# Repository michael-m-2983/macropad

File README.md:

# macropad

A custom macropad designed by me.

## BOM

| Qty | Item            | Source | Details                                                |
| --- | --------------- | ------ | ------------------------------------------------------ |
| 1   | Case            |        | The case is two seperate parts. It will be 3D printed. |
| 1   | PCB             |        | Designed using KiCad.                                  |
| 1   | Microcontroller | Kit    | Using the Seeed XIAO RP2040                            |
| 1   | OLED Display    | Kit    | 0.91"                                                  |
| 5   | Switch          | Kit    | "MX-style"                                             |
| 5   | Keycaps         | Kit    | Blank white DSA keycaps                                |
| 1   | Rotary Encoder  | Kit    | EC11, Alps                                             |
| 4   | Screws          | Kit    | M3x16mm                                                |

## Components

### Case

The case was designed using [onshape](https://onshape.com/).

It is seperated into two pieces: 

#### Case Top

The top piece has holes for the buttons, OLED screen, rotary encoder, and the screws to attach it to the bottom part.

#### Case Bottom

The bottom part of the case is composed of a baseplate and four walls that are on top of it. The four corners of the walls have holes for screws meant to attach the top part of the case. The wall nearest to the MCU has a hole for the USB-C connector so that it can be accessed easily.

### PCB

The PCB was designed with [KiCad](https://www.kicad.org/), an open-source electronics design software. 

The design of the PCB started with a schematic that dictates which components must be connected to each other:

After this schematic was completed, the traces on the PCB had to be drawn. Here is what the final result looks like:

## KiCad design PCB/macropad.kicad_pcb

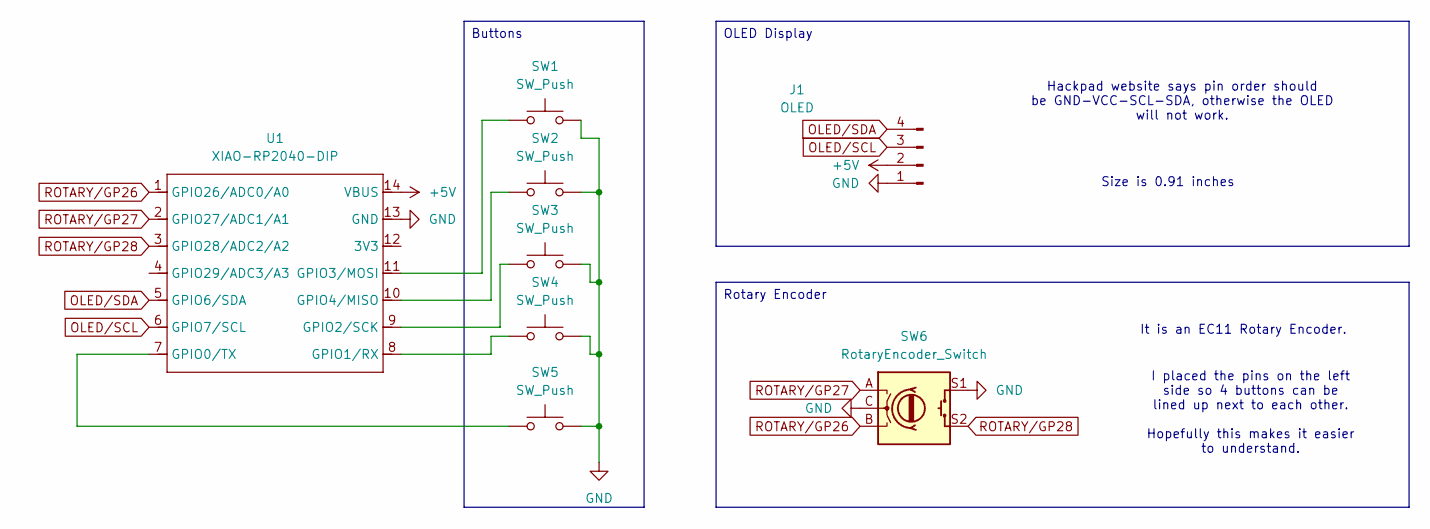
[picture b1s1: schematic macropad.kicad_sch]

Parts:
J1: OLED; SSD1306-0.91-OLED-4pin-128x32
SW1, SW2, SW3, SW4, SW5: SW_Push; SW_Cherry_MX_1.00u_PCB
SW6: RotaryEncoder_Switch; RotaryEncoder_Alps_EC11E-Switch_Vertical_H20mm
U1: XIAO-RP2040-DIP

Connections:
+5V: J1.2, U1.14 (VBUS)
GND: J1.1, SW1.2, SW2.2, SW3.2, SW4.2, SW5.2, SW6.C, SW6.S1, U1.13 (GND)
unnamed: SW5.1, U1.7 (GPIO0/TX)
unnamed: SW4.1, U1.8 (GPIO1/RX)
unnamed: SW3.1, U1.9 (GPIO2/SCK)
unnamed: SW1.1, U1.11 (GPIO3/MOSI)
unnamed: SW2.1, U1.10 (GPIO4/MISO)
OLED/SCL: J1.3, U1.6 (GPIO7/SCL)
OLED/SDA: J1.4, U1.5 (GPIO6/SDA)
ROTARY/GP26: SW6.B, U1.1 (GPIO26/ADC0/A0)
ROTARY/GP27: SW6.A, U1.2 (GPIO27/ADC1/A1)
ROTARY/GP28: SW6.S2, U1.3 (GPIO28/ADC2/A2)

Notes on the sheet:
Hackpad website says pin order should be GND-VCC-SCL-SDA, otherwise the OLED will not work.
I placed the pins on the left side so 4 buttons can be lined up next to each other. Hopefully this makes it easier to understand.
Size is 0.91 inches
It is an EC11 Rotary Encoder.
Buttons
OLED Display
Rotary Encoder

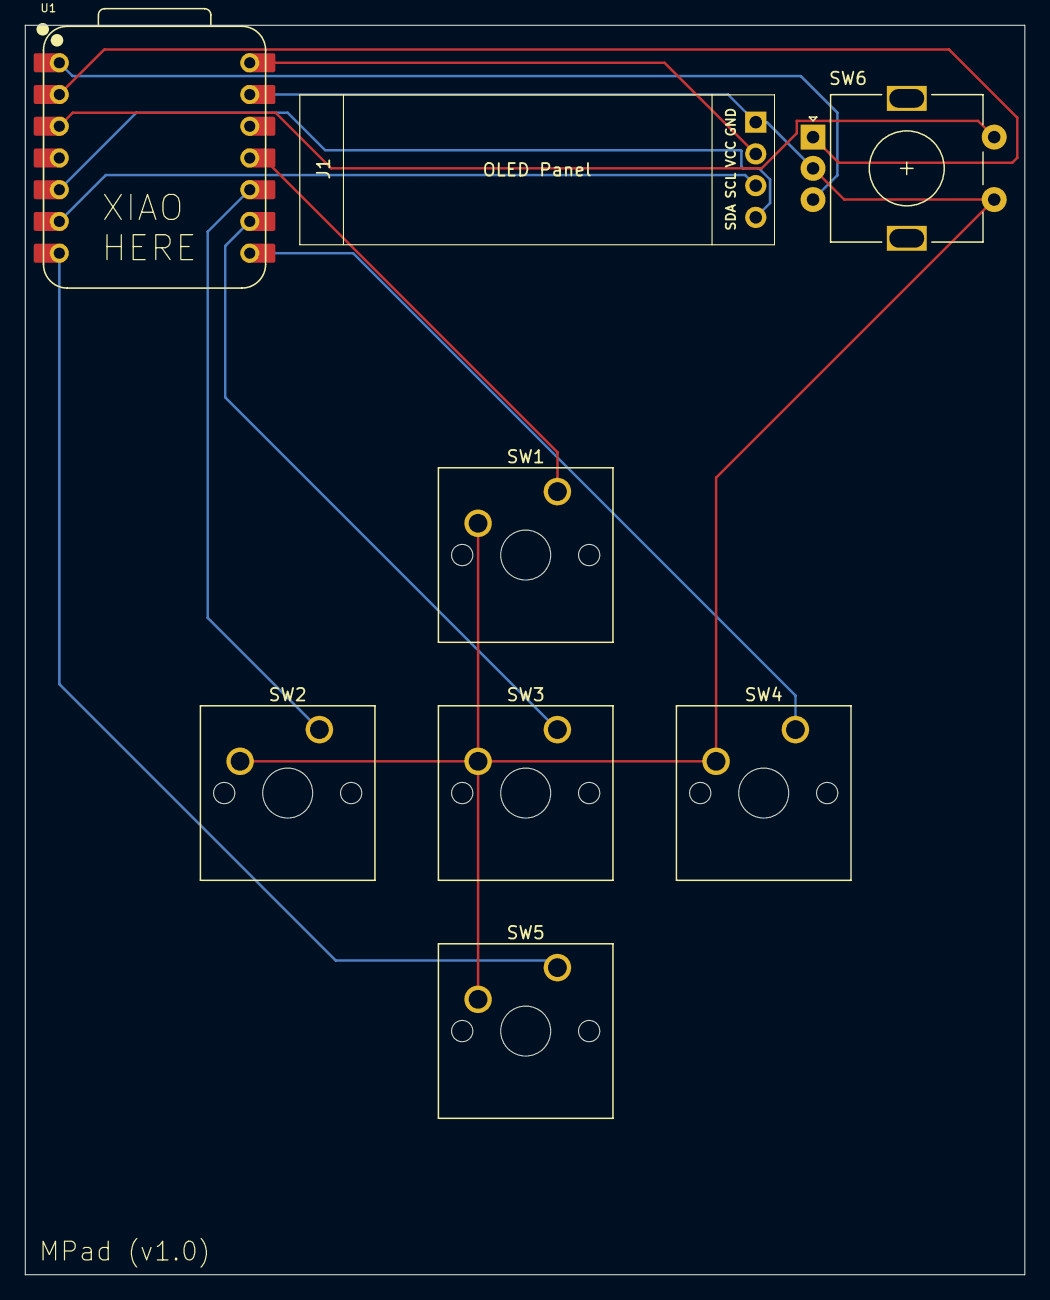
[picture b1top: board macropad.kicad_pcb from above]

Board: 2 copper layers, 80.0 x 100.0 mm, 8 parts (0 on the bottom side), 12 nets.

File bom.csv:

"Reference","Value","Footprint","Datasheet","Qty","DNP","Exclude from BOM","Exclude from Board"
"J1","OLED","OLED:SSD1306-0.91-OLED-4pin-128x32","~","1","","",""
"SW1,SW2,SW3,SW4,SW5","SW_Push","Button_Switch_Keyboard:SW_Cherry_MX_1.00u_PCB","~","5","","",""
"SW6","RotaryEncoder_Switch","RotaryEncoder:RotaryEncoder_Alps_EC11E-Switch_Vertical_H20mm","~","1","","",""
"U1","XIAO-RP2040-DIP","OPL:XIAO-RP2040-DIP","https://files.seeedstudio.com/wiki/XIAO-RP2040/res/rp2040_da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","1","","",""

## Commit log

2025-07-29 README updates
2025-07-29 Make image backgrounds transparent
2025-07-29 Add exploded render
2025-07-29 Implement arrow keys in firmware
2025-07-29 Align README images
2025-07-30 Add additional KiCad files
